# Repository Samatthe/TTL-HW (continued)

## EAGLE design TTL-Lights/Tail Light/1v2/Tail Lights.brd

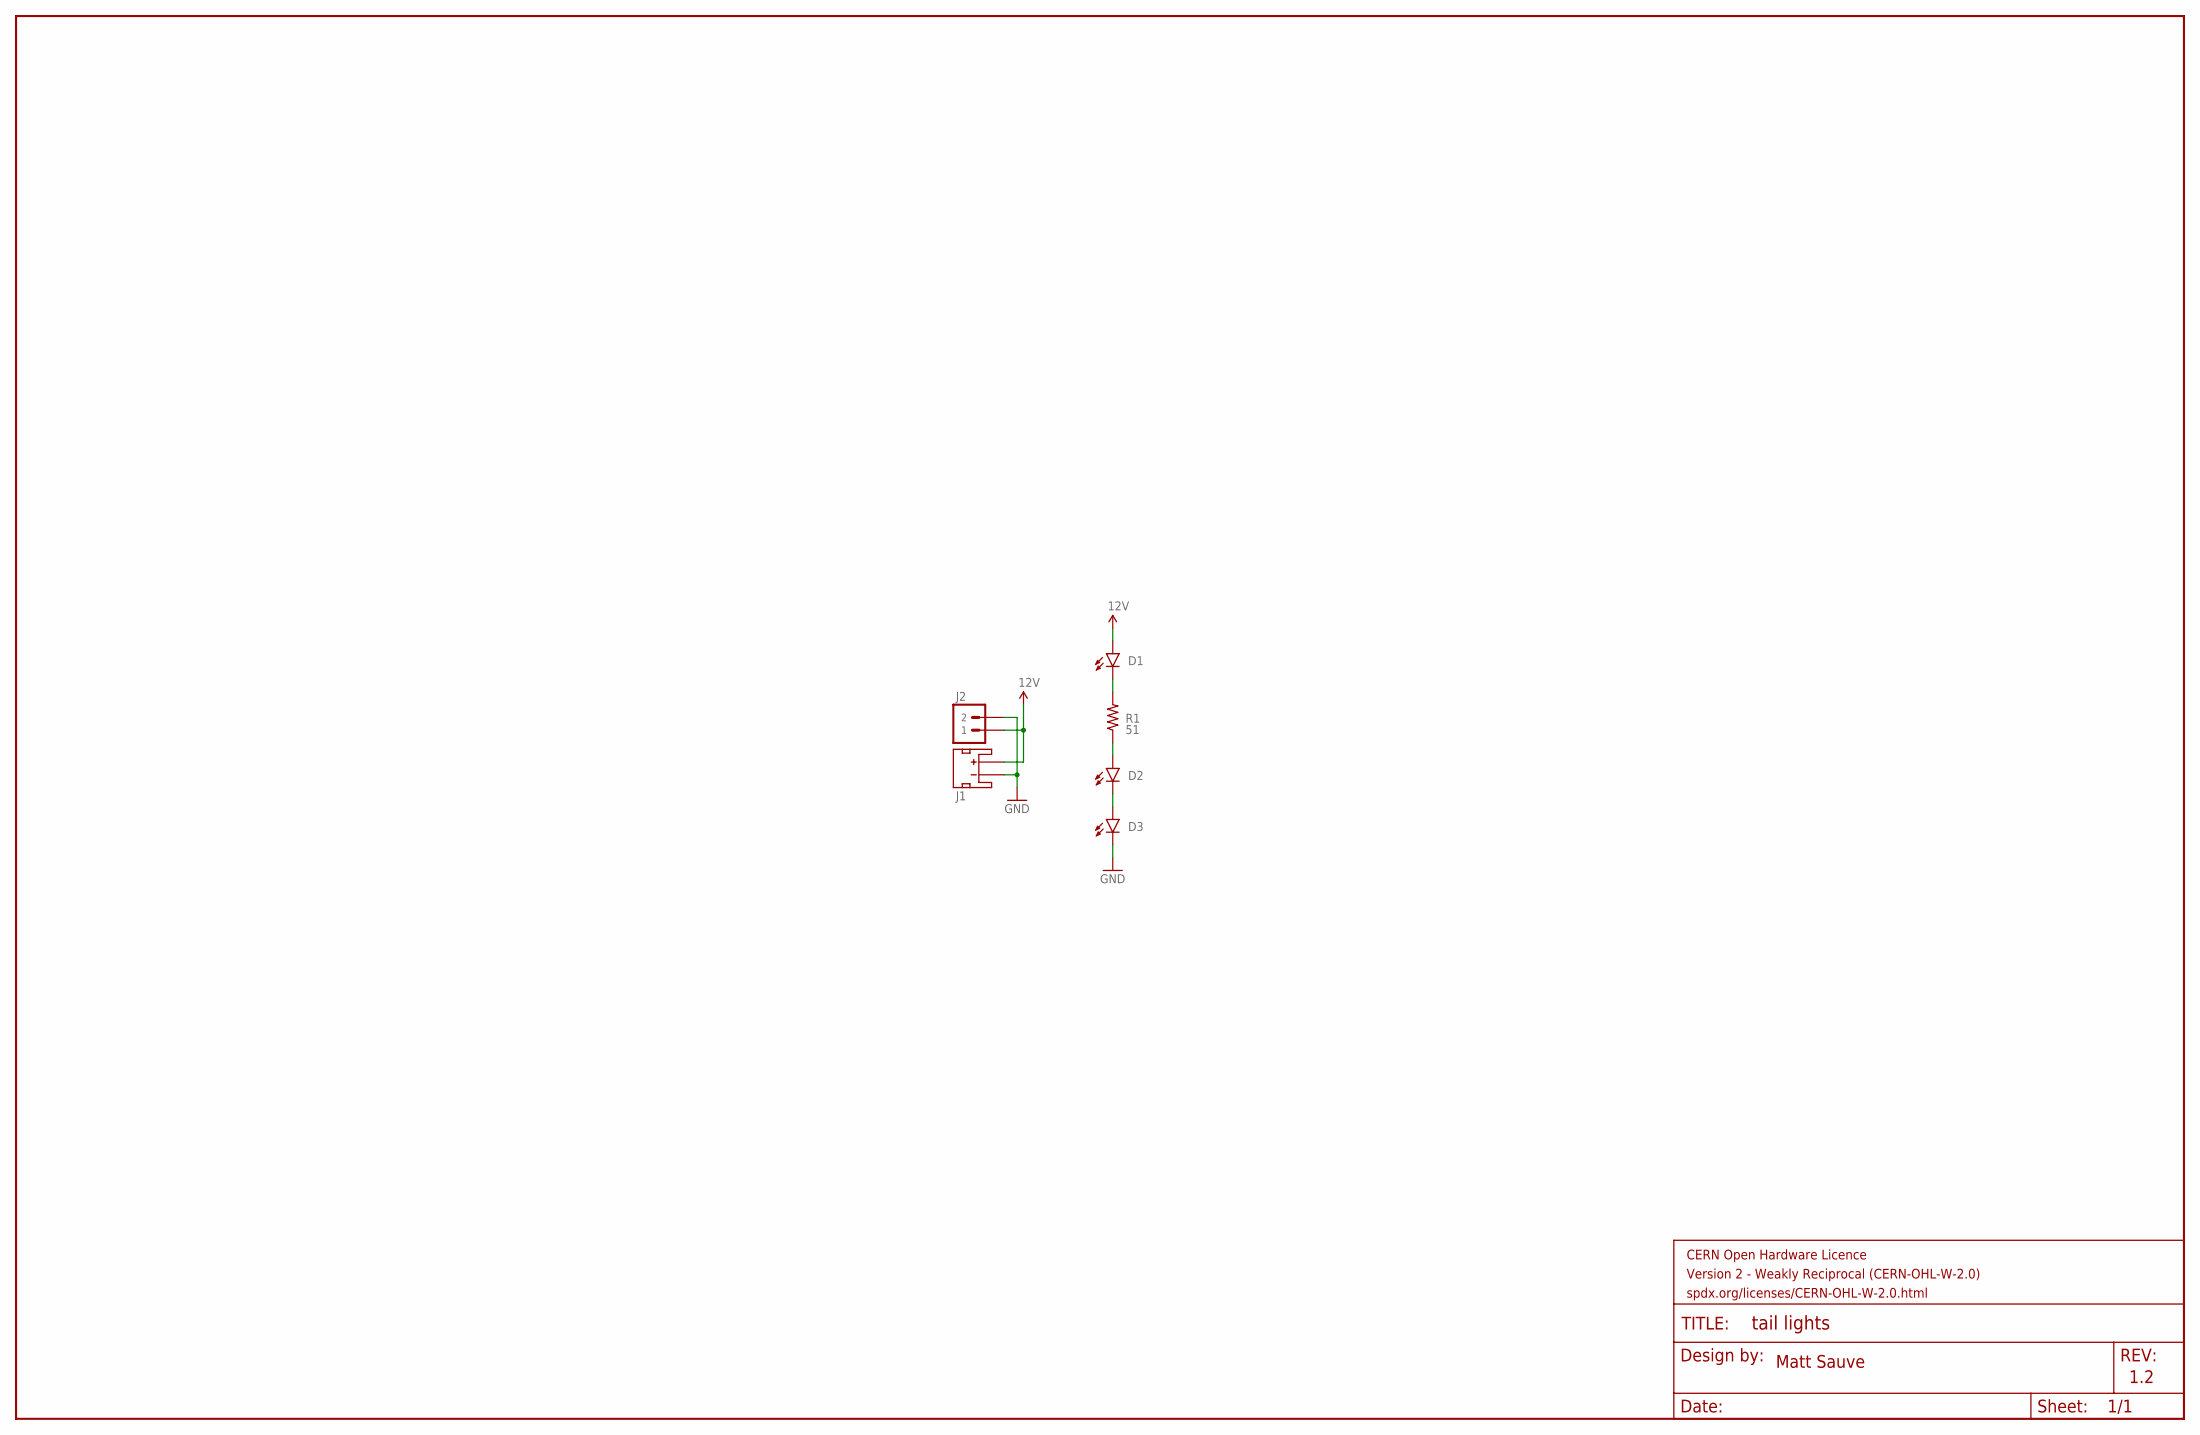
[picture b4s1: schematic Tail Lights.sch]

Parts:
D1, D2, D3: RED_CREE_LED; 4-SMD
FRAME1: FRAME-LEDGER_CERN_WEAK; CERN_WEAK
J1: JST_2MM_MALE; JST-2-SMD
J2: JST_PH_2POS
R1: 51; R2512

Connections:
12V: D1.P$1 (A), D1.P$2 (A), J1.2 (+), J2.1
GND: D3.P$3 (C), D3.P$4 (C), J1.1 (-), J2.2
unnamed: D2.P$1 (A), D2.P$2 (A), R1.1
unnamed: D1.P$3 (C), D1.P$4 (C), R1.2
unnamed: D2.P$3 (C), D2.P$4 (C), D3.P$1 (A), D3.P$2 (A)

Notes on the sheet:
Matt Sauve
1.2

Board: 2 copper layers, 7 parts (2 on the bottom side), 5 nets, no tracks yet.

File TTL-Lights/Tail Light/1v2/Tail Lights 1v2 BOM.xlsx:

Parts | Value | Device | Package
J1 |  | JST_2MM_MALE | JST-2-SMD
R1 | 51 | RESISTOR2512 | 2512
J2 |  | JST_PH_2POS | JST_PH_2POS
D1 |  | MLERED-A1-0000-000V01
D2 |  | MLERED-A1-0000-000V01 | 4-SMD
D3 |  | MLERED-A1-0000-000V01 | 4-SMD

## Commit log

2023-09-26 Initial Commit of Design Files
